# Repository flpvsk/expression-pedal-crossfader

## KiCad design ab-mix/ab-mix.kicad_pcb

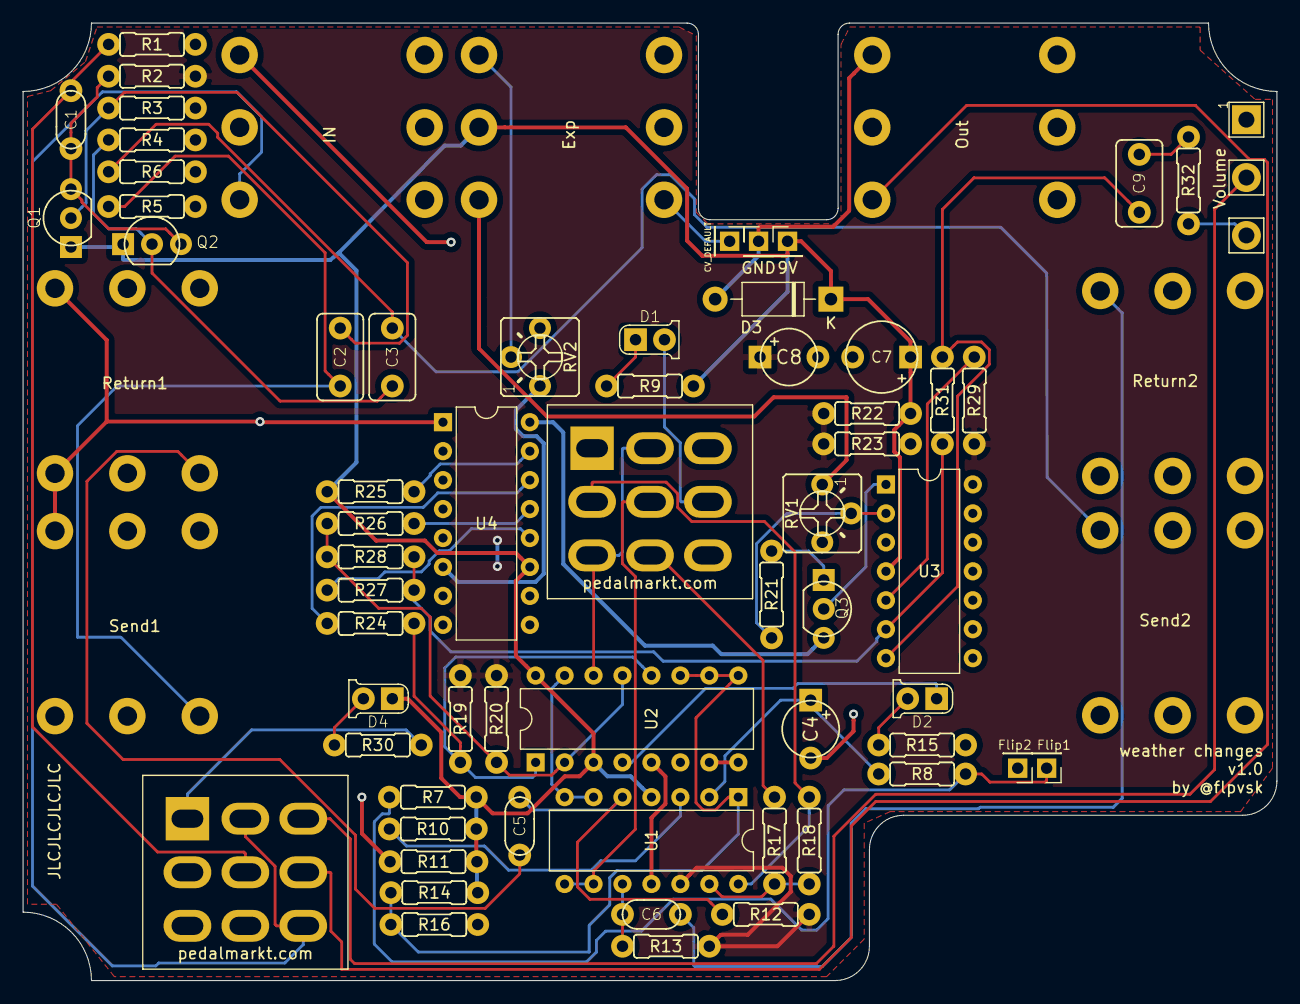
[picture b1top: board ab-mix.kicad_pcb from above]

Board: 2 copper layers, 110.0 x 84.0 mm, 69 parts (0 on the bottom side), 50 nets.

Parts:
C1, C5, C6: .1u; 0.2%22.SML
C2, C3, C9: 1u; 0.2%22.MED
C4: 10u; 0504
C7: 100u; 0633
C8: 47u; 0504
D1: Phase; 3MM_1
D2: Flip; 3MM_1
D3: 1N4001; D_DO-41_SOD81_P10.16mm_Horizontal
D4: Bypass; 3MM_1
H1: Flip1; PinHeader_1x01_P2.54mm_Vertical_Front_Back
H2: Flip2; PinHeader_1x01_P2.54mm_Vertical_Front_Back
H3: 9V; PinHeader_1x01_P2.54mm_Vertical_Front_Back
H4: GND; PinHeader_1x01_P2.54mm_Vertical_Front_Back
H5: CV_DEFAULT; PinHeader_1x01_P2.54mm_Vertical_Front_Back
J1: IN; Jack_6.35mm_Neutrik_NMJ6HCD3_Horizontal
J2: Out; Jack_6.35mm_Neutrik_NMJ6HCD3_Horizontal
J3: Send1; Jack_6.35mm_Neutrik_NMJ6HCD3_Horizontal
J4: Return1; Jack_6.35mm_Neutrik_NMJ6HCD3_Horizontal
J5: Send2; Jack_6.35mm_Neutrik_NMJ6HCD3_Horizontal
J6: Return2; Jack_6.35mm_Neutrik_NMJ6HCD3_Horizontal
J7: Exp; Jack_6.35mm_Neutrik_NMJ6HCD3_Horizontal
Q1, Q2: J201; TO92
Q3: Q_PNP_EBC; TO92
R1: 10M; 0.3_22.B
R2, R12, R13, R19, R20: 1M; 0.3_22.B
R3, R4, R10, R11, R24, R25, R26: 10K; 0.3_22.B
R5, R6, R16: 100K; 0.3_22.B
R7: 2.4K; 0.3_22.B
R8: 470; 0.3_22.B
R9, R15, R30: Rled; 0.3_22.B
R14: 7.5K; 0.3_22.B
R17, R18, R21, R32: 1K; 0.3_22.B
R22, R23, R27, R28, R29, R31: 10k; 0.3_22.B
RV1: 10K; TRIM1
RV2: 5K; TRIM1
RV3: Volume; 16MM_B.MOUNT
SW1: Phase; 3PDT.LUGS.FLPVSK
SW2: Bypass; 3PDT.LUGS.FLPVSK
U1, U3: LM324; DIP-14_W7.62mm
U2: CD4053B; DIP-16_W7.62mm
U4: LM13700; DIP-16_W7.62mm

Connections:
+4V5: C8.1, R2.2, R12.1, R13.1, R19.2, R20.2, R22.2, R23.1, R29.2, U1.12
+9V: C7.1, D3.1, D4.2, H3.1, J7.R, Q1.1, Q2.1, R7.2, R9.2, R10.1, R11.2, R14.2, R22.1, R25.2, U1.4, U2.3, U2.16, U3.4, U4.11
CI: Q3.3, U4.16
CV: J7.T, RV1.1
FLIP_IN1: U1.6, U1.7, U2.15
FLIP_IN2: SW1.3, SW1.4, U2.14
FLIP_OUT1: R19.1, R24.2, U2.1, U2.12
FLIP_OUT2: R20.1, R26.2, R28.2, U2.2, U2.13
FX_RETURN1: C5.1, J4.T
FX_RETURN2: C6.1, J6.T
FX_SEND1: C2.2, J3.T, R5.2
FX_SEND2: C3.2, J5.T, R6.2
GND: C4.2, C7.2, C8.2, D3.2, H2.1, H4.1, J1.S, J1.SN, J2.S, J2.SN, J3.S, J3.SN, J4.S, J4.SN, J5.S, J5.SN, J6.S, J6.SN, R1.1, R3.1, R4.1, R5.1, R6.1, R11.1, R15.2, R16.1, R23.2, RV2.1, RV3.1, SW1.9, SW2.2, SW2.3, SW2.6, U1.11, U2.5, U2.6, U2.7, U2.8, U3.3, U3.11, U4.1, U4.6
IN: C1.1, R1.2, SW2.5
JACK_IN: J1.T, SW2.4, SW2.9
JACK_OUT: J2.T, SW2.8
MIXER_IN: R27.1, R28.1, R31.2, U3.6
unnamed: C1.2, Q1.3, Q2.3, R2.1
unnamed: C2.1, Q1.2, R3.2
unnamed: C3.1, Q2.2, R4.2
unnamed: C4.1, R8.1, U1.2
unnamed: C5.2, R12.2, U1.5
unnamed: C6.2, R13.2, U1.10
unnamed: C9.1, R32.2
unnamed: C9.2, R31.1, U3.7
unnamed: D1.1, SW1.8
unnamed: D1.2, R9.1
unnamed: D2.1, R15.1
unnamed: D2.2, U2.4
unnamed: D4.1, R30.1
unnamed: H1.1, R7.1, R8.2
unnamed: H5.1, J7.TN
unnamed: J7.S, RV2.2
unnamed: Q3.1, R21.1
unnamed: Q3.2, U3.1
unnamed: R10.2, U1.3
unnamed: R14.1, R16.2, U1.1, U2.9, U2.10, U2.11
unnamed: R17.1, R18.2, U1.13
unnamed: R17.2, SW1.6
unnamed: R18.1, SW1.2, U1.14
unnamed: R21.2, RV1.2, U3.2
unnamed: R24.1, U4.14
unnamed: R25.1, U4.15
unnamed: R26.1, U4.13
unnamed: R27.2, U4.12
unnamed: R29.1, U3.5
unnamed: R30.2, SW2.1
unnamed: R32.1, RV3.3
unnamed: SW1.5, U1.8, U1.9
OUT: RV3.2, SW2.7

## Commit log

2020-11-21 Init
2020-11-24 Placed Jacks and Switches
2020-11-24 All jacks and the pot placed
2020-11-24 Edge cuts done
2020-11-24 Power section
2020-11-24 More power section
2020-11-25 First two chips 😭
2020-11-25 That LAST connection!
2020-11-25 Is it done?!?!?!
2020-11-25 Gerbers generated
2021-07-13 v2 init
